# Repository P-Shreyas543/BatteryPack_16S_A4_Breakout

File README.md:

# 14S 18650 Battery Pack Breakout (A4)

KiCad 10 project for a 14S (58.8 V max, 50.4 V nominal) 18650 battery pack on a 297 × 210 mm (A4) 4-layer PCB, built as a BMS breakout and training board.

## Layout architecture
- **Cells:** two mirrored columns of 7. Cells 1–7 run down the left column and cells 8–14 up the right. Every row uses the same **27.6 mm pitch**, so every cell has a 4.8 mm air gap on each side.
- **Equal cell-to-cell resistance (ACIR):** all 13 cell-to-cell links are the same copper strap on F.Cu and B.Cu. The 12 in-column straps are identical 10 mm bars at the holder ends. The cell 7→8 strap across the channel is widened to 16.15 mm so its resistance matches. Checked with a 2-D field solve (`tools/acir.py`, result in `docs/acir_check.txt`): **0.260 mΩ per link, 0.08 % spread**.
- **Centre channel = sense spine.** Each cell node has its own 60 V PPTC right next to it. One routed bus on In1 carries all 15 taps up to J1. NTC pairs run on In2.
- **Top edge = every connection.** Left to right: B− lug · HV indicator + pack TVS · **J1 balance** (centred) · **J2 NTC** · PACK+ lug · fuse.
- **Outer margins = per-cell service area.** Red/black test loops, the reverse-cell LED, and a writable box for cell voltage / IR.

## Symmetry
The board is mirror-symmetric about its vertical centre line. `tools/symcheck.py` lists every footprint without a same-type twin at the mirrored position:
- Mirrored or on the centre line: all 14 holders, the cell straps, the per-cell LED/test-loop groups (the series order of each LED string is chosen so twins use the same parts), the 6 side NTCs, the 12 side PPTCs, the TVS chain under J1, the lugs, holes and fiducials. PPTC 7, NTC4 and J1 sit on the centre line.
- One-of-a-kind, by design: the J2 NTC header (mirrored by the HV indicator + pack TVS block) and the single PACK+ fuse with its blown LED.
- Cell polarity alternates down each column. Because the pack is one series string, the right column's polarity is the reverse of the left's.

## Parts (all JLCPCB / LCSC)
| Block | Parts |
|---|---|
| Cell holders | BH-18650-B1BA002 `C2988620` |
| Per cell | Keystone 5000/5001 test loops (`C5199900` / `C238122`). Reverse-cell LED: 1k `C17513` + red LED `C84256` + 1N4148WS `C2128`. |
| J1 BMS balance | JST XH **B15B-XH-A** `C158020`. Pin 1 = B−, pin 15 = C14+. |
| Tap protection | MF-MSMF010-2 60 V PPTC `C12430` at every node. LKS05D3-B 5 V bidirectional TVS (SOD-323) `C2984829` across every cell, directly under J1. |
| J2 BMS NTC | JST XH **B14B-XH-A** `C158022` with 7× 10k B3950 NTC `C13879` saddled between cells. Pins 2n−1/2n = NTCn. |
| Power path | 5×20 fuse holder `C268205` (fit 10 A), M4 lugs T44009 `C481463`, SMCJ70CA `C840779` |

NTC map: NTC1 = C1/C2, NTC2 = C3/C4, NTC3 = C5/C6 (left column), **NTC4 = board centre line on the cell 7→8 bus**, NTC5 = C13/C14, NTC6 = C11/C12, NTC7 = C9/C10 (right column).

## How to connect
1. Plug the BMS balance lead into **J1** (B− wire on pin 1).
2. Plug the BMS NTC lead into **J2**, or leave it unplugged.
3. Connect the **B− lug** to the BMS B− pad, and the **PACK+ lug** to the load or charger +.
4. Connect the load or charger − to the BMS P−.
5. Insert the cells last. A red LED beside a cell means it is in backwards.

## Files
- `fab/BatteryPack_14S_A4_gerbers.zip`, `fab/JLCPCB_BOM.csv`, `fab/JLCPCB_CPL.csv`: fabrication and assembly files. Check part rotations in JLC's preview.
- `fab/erc.rpt`, `fab/drc.rpt`: 0 ERC violations, 0 DRC violations, 0 unconnected items, 0 schematic-parity issues.
- `docs/`: schematic PDF, renders, and the ACIR check.
- `tools/`: generators. `symcheck.py` runs the symmetry audit. `design.py` holds the parts and nets, `geom.py` the board geometry, `gen_sch.py` / `gen_pcb.py` build the files, and `acir.py` runs the link-resistance check. To rebuild everything, run `tools/build.sh` in the `kicad/kicad:10.0` docker image.

Side-entry XH headers (S15B) are out of stock at LCSC, so the top-entry headers sit right on the top edge. Re-check LCSC stock before ordering. The holder, the test loops and the SOD-323 TVS have the lowest stock.

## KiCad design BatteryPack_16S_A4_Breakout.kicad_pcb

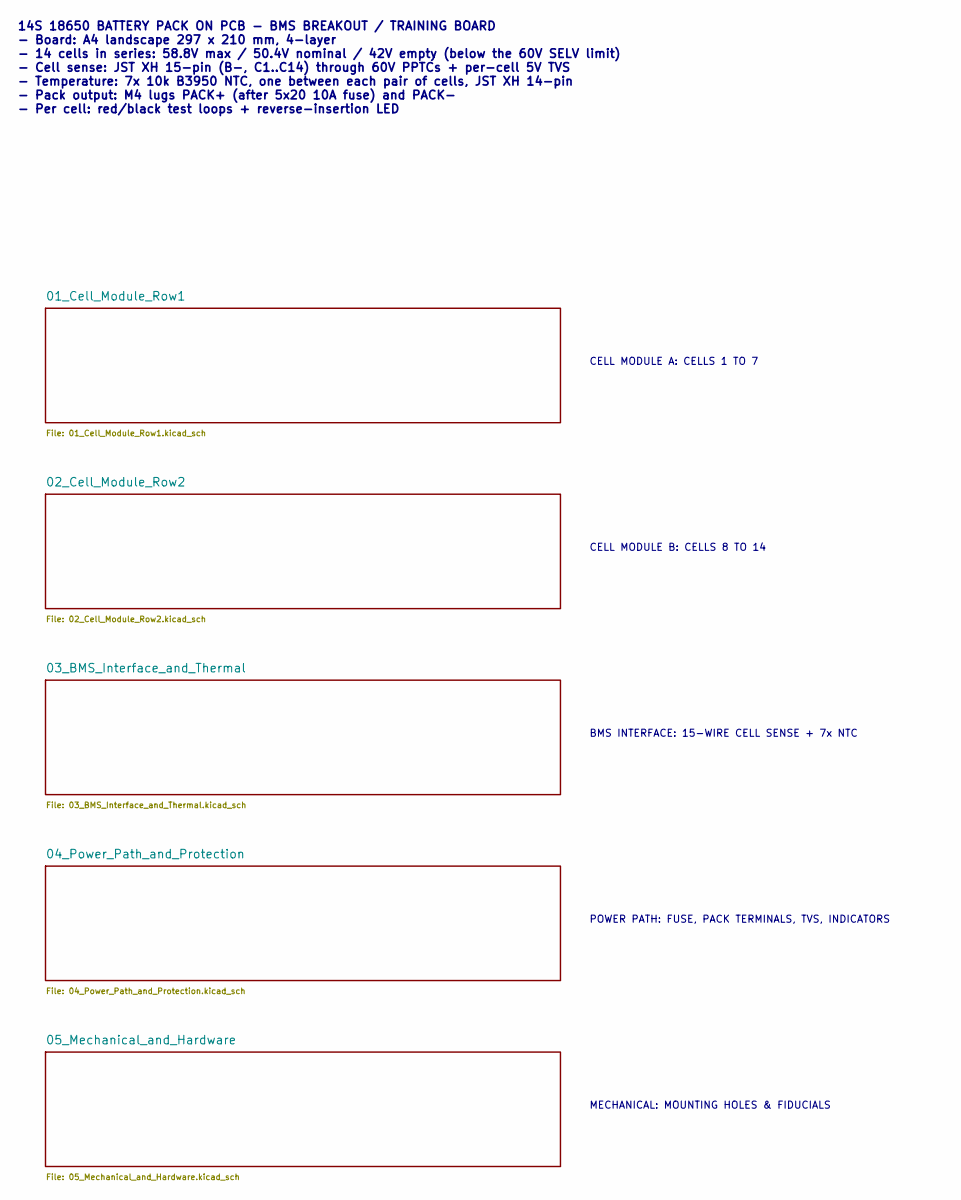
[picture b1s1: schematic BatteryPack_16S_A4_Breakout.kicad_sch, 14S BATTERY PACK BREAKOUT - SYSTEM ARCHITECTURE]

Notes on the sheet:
MECHANICAL: MOUNTING HOLES & FIDUCIALS
CELL MODULE B: CELLS 8 TO 14
BMS INTERFACE: 15-WIRE CELL SENSE + 7x NTC
POWER PATH: FUSE, PACK TERMINALS, TVS, INDICATORS
14S 18650 BATTERY PACK ON PCB - BMS BREAKOUT / TRAINING BOARD - Board: A4 landscape 297 x 210 mm, 4-layer - 14 cells in series: 58.8V max / 50.4V nominal / 42V empty (below the 60V SELV limit) - Cell sense: JST XH 15-pin (B-, C1..C14) through 60V PPTCs + per-cell 5V TVS - Temperature: 7x 10k B3950 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
CELL MODULE A: CELLS 1 TO 7

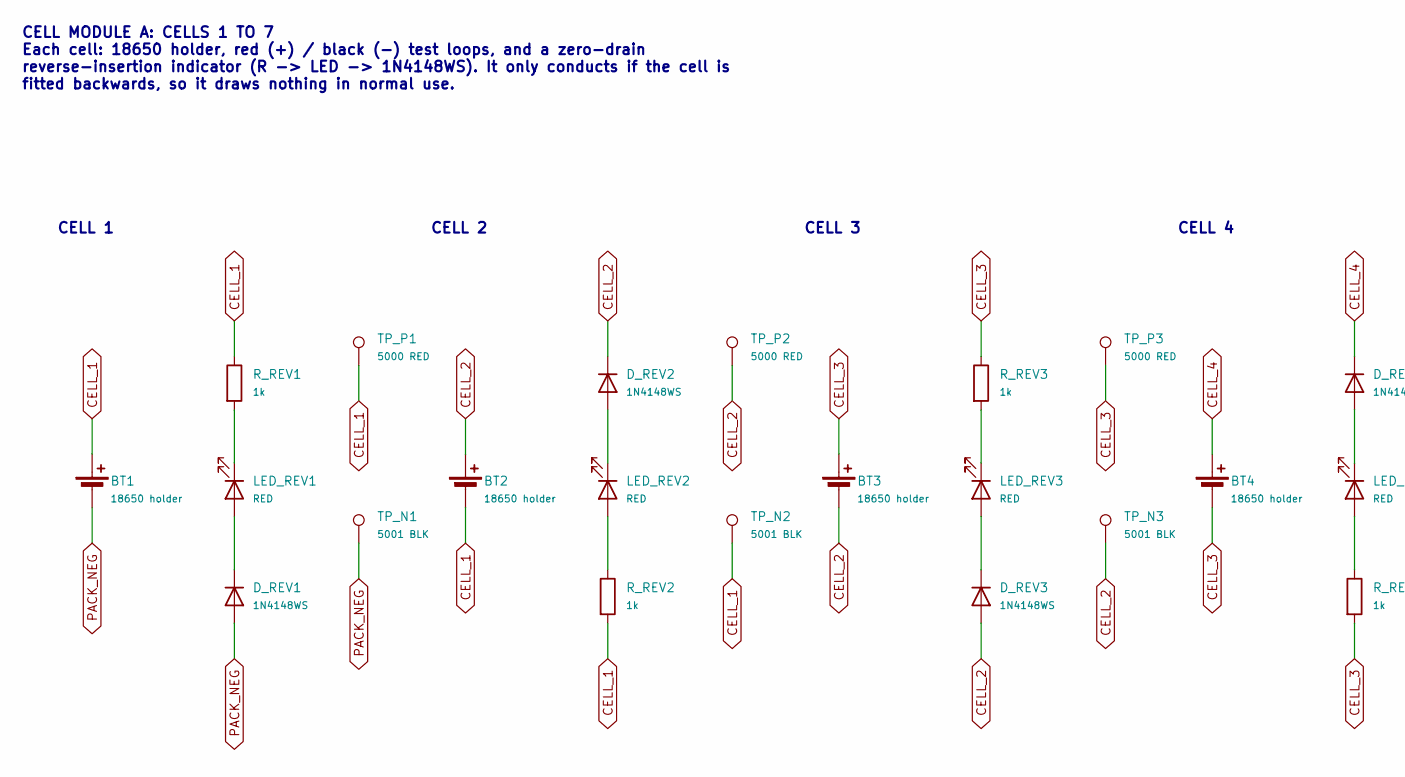
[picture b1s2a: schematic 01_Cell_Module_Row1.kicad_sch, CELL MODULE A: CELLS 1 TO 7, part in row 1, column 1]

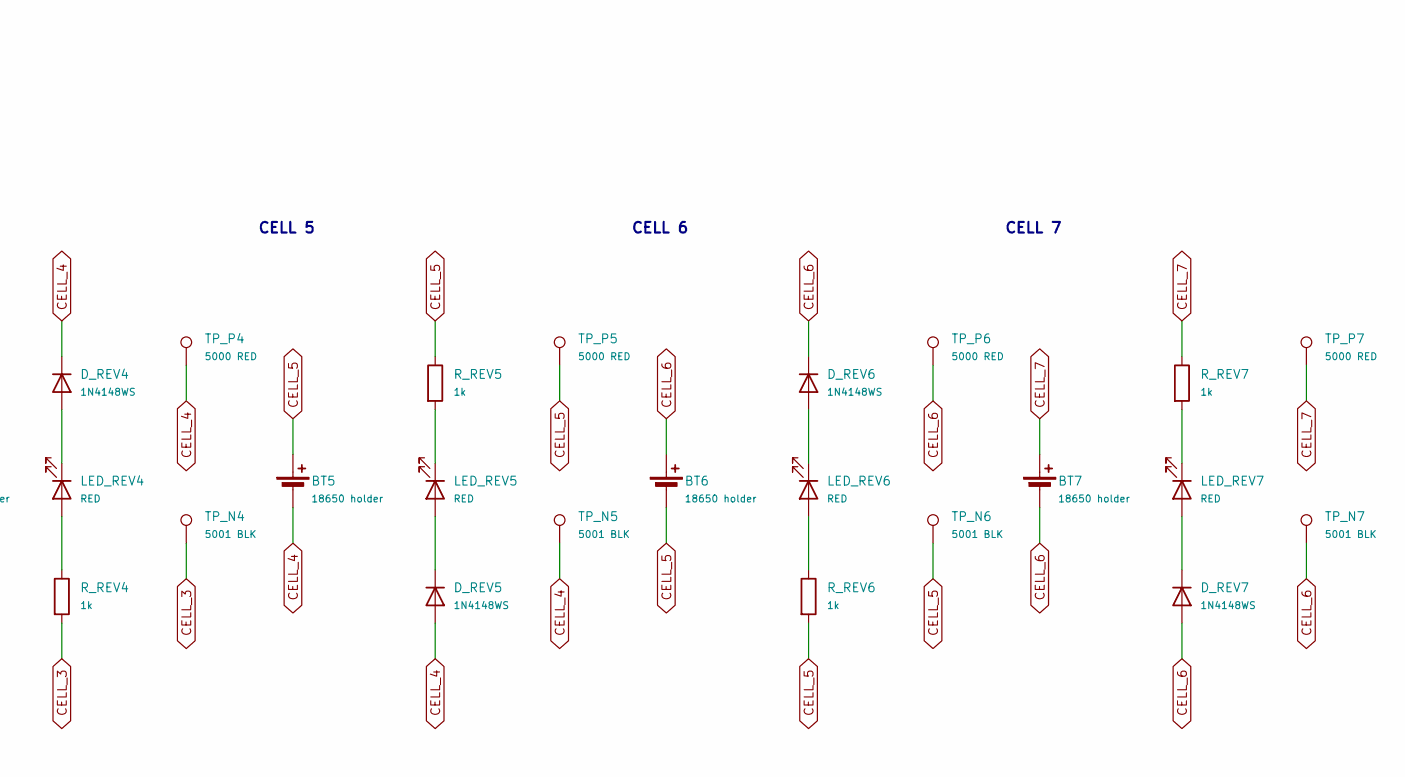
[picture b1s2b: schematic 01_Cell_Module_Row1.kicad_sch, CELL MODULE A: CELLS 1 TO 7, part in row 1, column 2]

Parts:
BT1, BT2, BT3, BT4, BT5, BT6, BT7: 18650 holder; BH18650B1BA002; MPN BH-18650-B1BA002; LCSC C2988620
D_REV1, D_REV2, D_REV3, D_REV4, D_REV5, D_REV6, D_REV7: 1N4148WS; D_SOD-323; MPN 1N4148WS; LCSC C2128
LED_REV1, LED_REV2, LED_REV3, LED_REV4, LED_REV5, LED_REV6, LED_REV7: RED; LED_0805_2012Metric; MPN NCD0805R1; LCSC C84256
R_REV1, R_REV2, R_REV3, R_REV4, R_REV5, R_REV6, R_REV7: 1k; R_0805_2012Metric; MPN 0805W8F1001T5E; LCSC C17513
TP_N1, TP_N2, TP_N3, TP_N4, TP_N5, TP_N6, TP_N7: 5001 BLK; TestPoint_Keystone_5000-5004_Miniature; MPN 5001; LCSC C238122
TP_P1, TP_P2, TP_P3, TP_P4, TP_P5, TP_P6, TP_P7: 5000 RED; TestPoint_Keystone_5000-5004_Miniature; MPN 5000; LCSC C5199900

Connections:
CELL_1: BT1.1 (+), BT2.2 (-), R_REV1.1, R_REV2.2, TP_N2.1, TP_P1.1; also elsewhere on the board
CELL_2: BT2.1 (+), BT3.2 (-), D_REV2.1 (K), D_REV3.2 (A), TP_N3.1, TP_P2.1; also elsewhere on the board
CELL_3: BT3.1 (+), BT4.2 (-), R_REV3.1, R_REV4.2, TP_N4.1, TP_P3.1; also elsewhere on the board
CELL_4: BT4.1 (+), BT5.2 (-), D_REV4.1 (K), D_REV5.2 (A), TP_N5.1, TP_P4.1; also elsewhere on the board
CELL_5: BT5.1 (+), BT6.2 (-), R_REV5.1, R_REV6.2, TP_N6.1, TP_P5.1; also elsewhere on the board
CELL_6: BT6.1 (+), BT7.2 (-), D_REV6.1 (K), D_REV7.2 (A), TP_N7.1, TP_P6.1; also elsewhere on the board
CELL_7: BT7.1 (+), R_REV7.1, TP_P7.1; also elsewhere on the board
unnamed: D_REV1.1 (K), LED_REV1.2 (A)
unnamed: D_REV2.2 (A), LED_REV2.1 (K)
unnamed: D_REV3.1 (K), LED_REV3.2 (A)
unnamed: D_REV4.2 (A), LED_REV4.1 (K)
unnamed: D_REV5.1 (K), LED_REV5.2 (A)
unnamed: D_REV6.2 (A), LED_REV6.1 (K)
unnamed: D_REV7.1 (K), LED_REV7.2 (A)
unnamed: LED_REV1.1 (K), R_REV1.2
unnamed: LED_REV2.2 (A), R_REV2.1
unnamed: LED_REV3.1 (K), R_REV3.2
unnamed: LED_REV4.2 (A), R_REV4.1
unnamed: LED_REV5.1 (K), R_REV5.2
unnamed: LED_REV6.2 (A), R_REV6.1
unnamed: LED_REV7.1 (K), R_REV7.2
PACK_NEG: BT1.2 (-), D_REV1.2 (A), TP_N1.1; also elsewhere on the board

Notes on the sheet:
CELL 4
CELL 2
CELL 7
CELL 3
CELL 5
CELL 6
CELL 1
CELL MODULE A: CELLS 1 TO 7 Each cell: 18650 holder, red (+) / black (-) test loops, and a zero-drain reverse-insertion indicator (R -> LED -> 1N4148WS). It only conducts if the cell is fitted backwards, so it draws nothing in normal use.

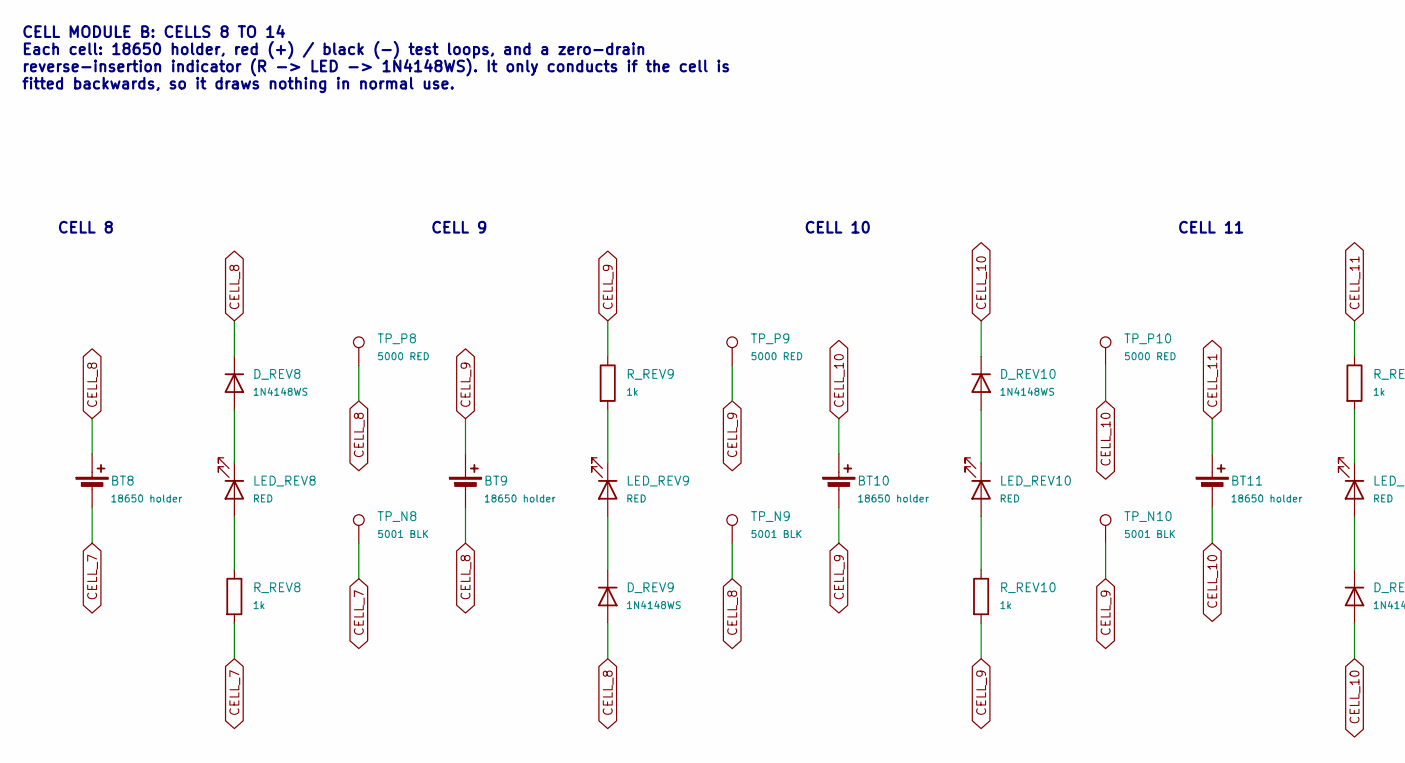
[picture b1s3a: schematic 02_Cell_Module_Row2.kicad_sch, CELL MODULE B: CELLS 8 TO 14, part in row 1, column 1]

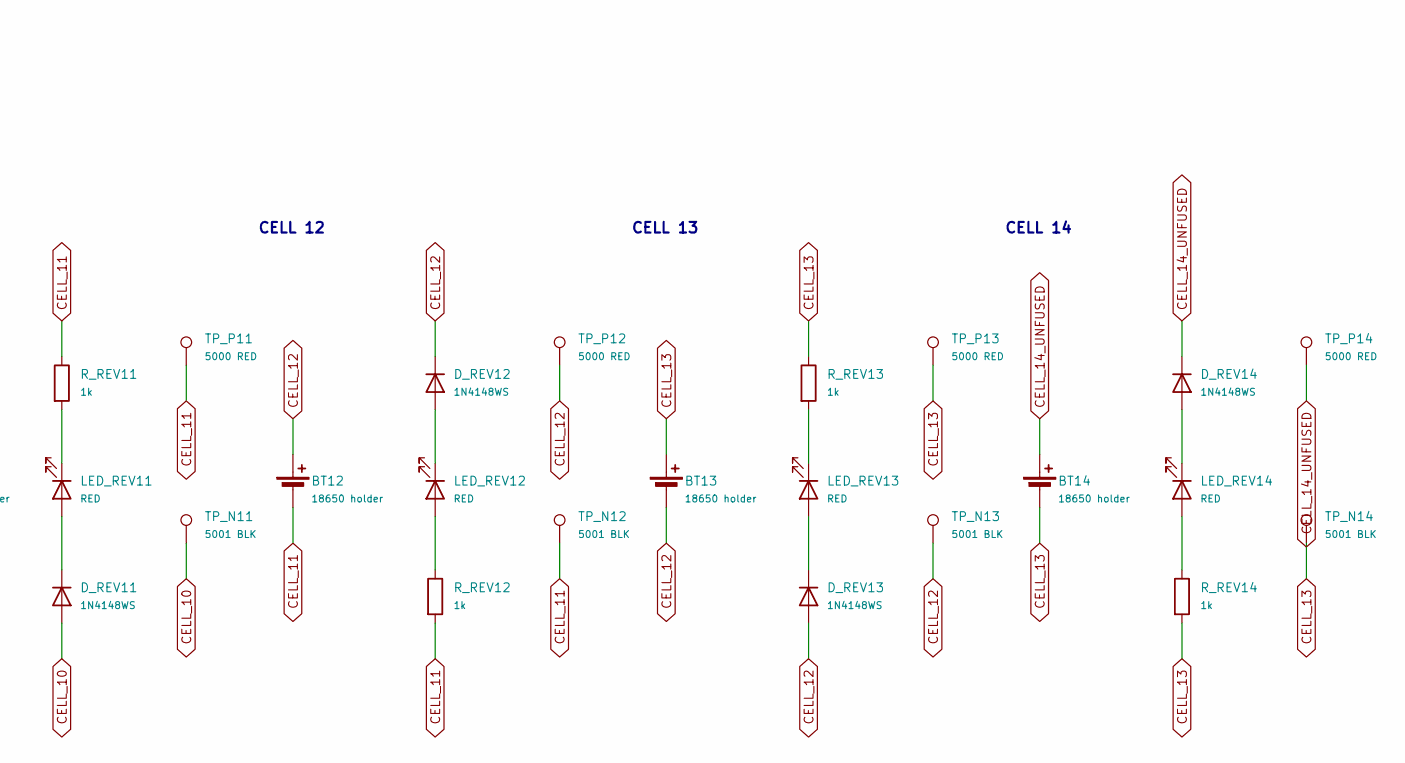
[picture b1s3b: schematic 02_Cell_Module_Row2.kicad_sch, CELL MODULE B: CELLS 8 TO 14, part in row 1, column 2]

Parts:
BT8, BT9, BT10, BT11, BT12, BT13, BT14: 18650 holder; BH18650B1BA002; MPN BH-18650-B1BA002; LCSC C2988620
D_REV8, D_REV9, D_REV10, D_REV11, D_REV12, D_REV13, D_REV14: 1N4148WS; D_SOD-323; MPN 1N4148WS; LCSC C2128
LED_REV8, LED_REV9, LED_REV10, LED_REV11, LED_REV12, LED_REV13, LED_REV14: RED; LED_0805_2012Metric; MPN NCD0805R1; LCSC C84256
R_REV8, R_REV9, R_REV10, R_REV11, R_REV12, R_REV13, R_REV14: 1k; R_0805_2012Metric; MPN 0805W8F1001T5E; LCSC C17513
TP_N8, TP_N9, TP_N10, TP_N11, TP_N12, TP_N13, TP_N14: 5001 BLK; TestPoint_Keystone_5000-5004_Miniature; MPN 5001; LCSC C238122
TP_P8, TP_P9, TP_P10, TP_P11, TP_P12, TP_P13, TP_P14: 5000 RED; TestPoint_Keystone_5000-5004_Miniature; MPN 5000; LCSC C5199900

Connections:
CELL_7: BT8.2 (-), R_REV8.2, TP_N8.1; also elsewhere on the board
CELL_8: BT8.1 (+), BT9.2 (-), D_REV8.1 (K), D_REV9.2 (A), TP_N9.1, TP_P8.1; also elsewhere on the board
CELL_9: BT9.1 (+), BT10.2 (-), R_REV9.1, R_REV10.2, TP_N10.1, TP_P9.1; also elsewhere on the board
CELL_10: BT10.1 (+), BT11.2 (-), D_REV10.1 (K), D_REV11.2 (A), TP_N11.1, TP_P10.1; also elsewhere on the board
CELL_11: BT11.1 (+), BT12.2 (-), R_REV11.1, R_REV12.2, TP_N12.1, TP_P11.1; also elsewhere on the board
CELL_12: BT12.1 (+), BT13.2 (-), D_REV12.1 (K), D_REV13.2 (A), TP_N13.1, TP_P12.1; also elsewhere on the board
CELL_13: BT13.1 (+), BT14.2 (-), R_REV13.1, R_REV14.2, TP_N14.1, TP_P13.1; also elsewhere on the board
CELL_14_UNFUSED: BT14.1 (+), D_REV14.1 (K), TP_P14.1; also elsewhere on the board
unnamed: D_REV8.2 (A), LED_REV8.1 (K)
unnamed: D_REV9.1 (K), LED_REV9.2 (A)
unnamed: D_REV10.2 (A), LED_REV10.1 (K)
unnamed: D_REV11.1 (K), LED_REV11.2 (A)
unnamed: D_REV12.2 (A), LED_REV12.1 (K)
unnamed: D_REV13.1 (K), LED_REV13.2 (A)
unnamed: D_REV14.2 (A), LED_REV14.1 (K)
unnamed: LED_REV8.2 (A), R_REV8.1
unnamed: LED_REV9.1 (K), R_REV9.2
unnamed: LED_REV10.2 (A), R_REV10.1
unnamed: LED_REV11.1 (K), R_REV11.2
unnamed: LED_REV12.2 (A), R_REV12.1
unnamed: LED_REV13.1 (K), R_REV13.2
unnamed: LED_REV14.2 (A), R_REV14.1

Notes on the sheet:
CELL 13
CELL MODULE B: CELLS 8 TO 14 Each cell: 18650 holder, red (+) / black (-) test loops, and a zero-drain reverse-insertion indicator (R -> LED -> 1N4148WS). It only conducts if the cell is fitted backwards, so it draws nothing in normal use.
CELL 9
CELL 14
CELL 12
CELL 8
CELL 10
CELL 11

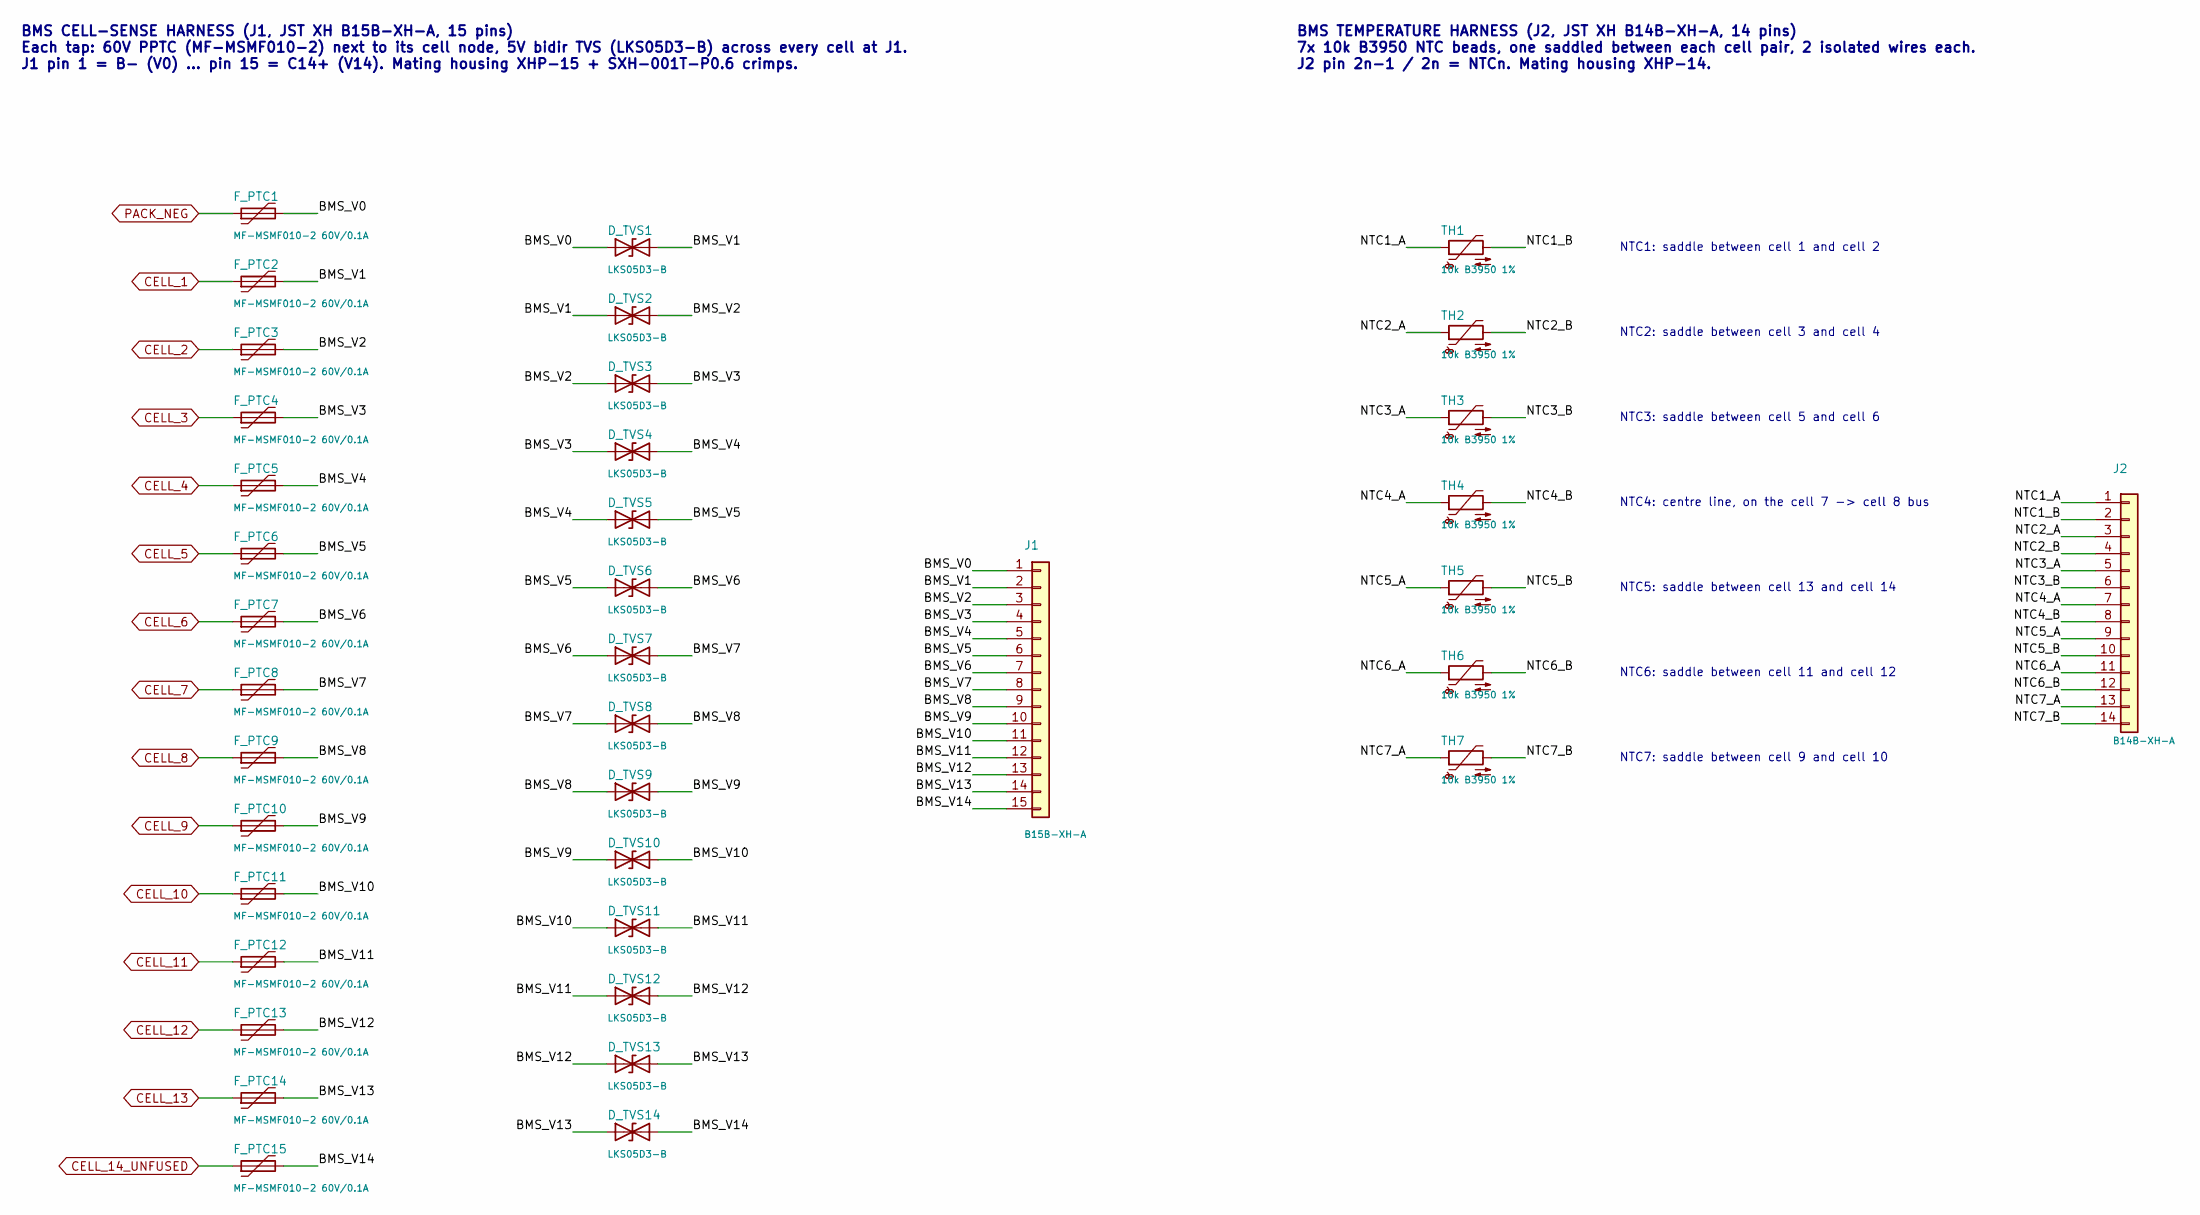
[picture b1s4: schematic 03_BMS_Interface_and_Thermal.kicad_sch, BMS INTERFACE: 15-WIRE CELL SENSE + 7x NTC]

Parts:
D_TVS1, D_TVS2, D_TVS3, D_TVS4, D_TVS5, D_TVS6, D_TVS7, D_TVS8, D_TVS9, D_TVS10, D_TVS11, D_TVS12, D_TVS13, D_TVS14: LKS05D3-B; D_SOD-323; MPN LKS05D3-B; LCSC C2984829
F_PTC1, F_PTC2, F_PTC3, F_PTC4, F_PTC5, F_PTC6, F_PTC7, F_PTC8, F_PTC9, F_PTC10, F_PTC11, F_PTC12, F_PTC13, F_PTC14, F_PTC15: MF-MSMF010-2 60V/0.1A; Fuse_1812_4532Metric; MPN MF-MSMF010-2; LCSC C12430
J1: B15B-XH-A; JST_XH_B15B-XH-A_1x15_P2.50mm_Vertical; MPN B15B-XH-A(LF)(SN); LCSC C158020
J2: B14B-XH-A; JST_XH_B14B-XH-A_1x14_P2.50mm_Vertical; MPN B14B-XH-A(LF)(SN); LCSC C158022
TH1, TH2, TH3, TH4, TH5, TH6, TH7: 10k B3950 1%; R_Axial_DIN0204_L3.6mm_D1.6mm_P2.54mm_Vertical; MPN MF52A103F3950; LCSC C13879

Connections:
/03_BMS_Interface_and_Thermal/BMS_V0: D_TVS1.1 (A1), F_PTC1.2, J1.1
/03_BMS_Interface_and_Thermal/BMS_V1: D_TVS1.2 (A2), D_TVS2.1 (A1), F_PTC2.2, J1.2
/03_BMS_Interface_and_Thermal/BMS_V2: D_TVS2.2 (A2), D_TVS3.1 (A1), F_PTC3.2, J1.3
/03_BMS_Interface_and_Thermal/BMS_V3: D_TVS3.2 (A2), D_TVS4.1 (A1), F_PTC4.2, J1.4
/03_BMS_Interface_and_Thermal/BMS_V4: D_TVS4.2 (A2), D_TVS5.1 (A1), F_PTC5.2, J1.5
/03_BMS_Interface_and_Thermal/BMS_V5: D_TVS5.2 (A2), D_TVS6.1 (A1), F_PTC6.2, J1.6
/03_BMS_Interface_and_Thermal/BMS_V6: D_TVS6.2 (A2), D_TVS7.1 (A1), F_PTC7.2, J1.7
/03_BMS_Interface_and_Thermal/BMS_V7: D_TVS7.2 (A2), D_TVS8.1 (A1), F_PTC8.2, J1.8
/03_BMS_Interface_and_Thermal/BMS_V8: D_TVS8.2 (A2), D_TVS9.1 (A1), F_PTC9.2, J1.9
/03_BMS_Interface_and_Thermal/BMS_V9: D_TVS9.2 (A2), D_TVS10.1 (A1), F_PTC10.2, J1.10
/03_BMS_Interface_and_Thermal/BMS_V10: D_TVS10.2 (A2), D_TVS11.1 (A1), F_PTC11.2, J1.11
/03_BMS_Interface_and_Thermal/BMS_V11: D_TVS11.2 (A2), D_TVS12.1 (A1), F_PTC12.2, J1.12
/03_BMS_Interface_and_Thermal/BMS_V12: D_TVS12.2 (A2), D_TVS13.1 (A1), F_PTC13.2, J1.13
/03_BMS_Interface_and_Thermal/BMS_V13: D_TVS13.2 (A2), D_TVS14.1 (A1), F_PTC14.2, J1.14
/03_BMS_Interface_and_Thermal/BMS_V14: D_TVS14.2 (A2), F_PTC15.2, J1.15
/03_BMS_Interface_and_Thermal/NTC1_A: J2.1, TH1.1
/03_BMS_Interface_and_Thermal/NTC1_B: J2.2, TH1.2
/03_BMS_Interface_and_Thermal/NTC2_A: J2.3, TH2.1
/03_BMS_Interface_and_Thermal/NTC2_B: J2.4, TH2.2
/03_BMS_Interface_and_Thermal/NTC3_A: J2.5, TH3.1
/03_BMS_Interface_and_Thermal/NTC3_B: J2.6, TH3.2
/03_BMS_Interface_and_Thermal/NTC4_A: J2.7, TH4.1
/03_BMS_Interface_and_Thermal/NTC4_B: J2.8, TH4.2
/03_BMS_Interface_and_Thermal/NTC5_A: J2.9, TH5.1
/03_BMS_Interface_and_Thermal/NTC5_B: J2.10, TH5.2
/03_BMS_Interface_and_Thermal/NTC6_A: J2.11, TH6.1
/03_BMS_Interface_and_Thermal/NTC6_B: J2.12, TH6.2
/03_BMS_Interface_and_Thermal/NTC7_A: J2.13, TH7.1
/03_BMS_Interface_and_Thermal/NTC7_B: J2.14, TH7.2
CELL_1: F_PTC2.1; also elsewhere on the board
CELL_2: F_PTC3.1; also elsewhere on the board
CELL_3: F_PTC4.1; also elsewhere on the board
CELL_4: F_PTC5.1; also elsewhere on the board
CELL_5: F_PTC6.1; also elsewhere on the board
CELL_6: F_PTC7.1; also elsewhere on the board
CELL_7: F_PTC8.1; also elsewhere on the board
CELL_8: F_PTC9.1; also elsewhere on the board
CELL_9: F_PTC10.1; also elsewhere on the board
CELL_10: F_PTC11.1; also elsewhere on the board
CELL_11: F_PTC12.1; also elsewhere on the board
CELL_12: F_PTC13.1; also elsewhere on the board
CELL_13: F_PTC14.1; also elsewhere on the board
CELL_14_UNFUSED: F_PTC15.1; also elsewhere on the board
PACK_NEG: F_PTC1.1; also elsewhere on the board

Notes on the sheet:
BMS TEMPERATURE HARNESS (J2, JST XH B14B-XH-A, 14 pins) 7x 10k B3950 NTC beads, one saddled between each cell pair, 2 isolated wires each. J2 pin 2n-1 / 2n = NTCn. Mating housing XHP-14.
NTC6: saddle between cell 11 and cell 12
NTC2: saddle between cell 3 and cell 4
NTC3: saddle between cell 5 and cell 6
NTC5: saddle between cell 13 and cell 14
NTC4: centre line, on the cell 7 -> cell 8 bus
BMS CELL-SENSE HARNESS (J1, JST XH B15B-XH-A, 15 pins) Each tap: 60V PPTC (MF-MSMF010-2) next to its cell node, 5V bidir TVS (LKS05D3-B) across every cell at J1. J1 pin 1 = B- (V0) ... pin 15 = C14+ (V14). Mating housing XHP-15 + SXH-001T-P0.6 crimps.
NTC1: saddle between cell 1 and cell 2
NTC7: saddle between cell 9 and cell 10

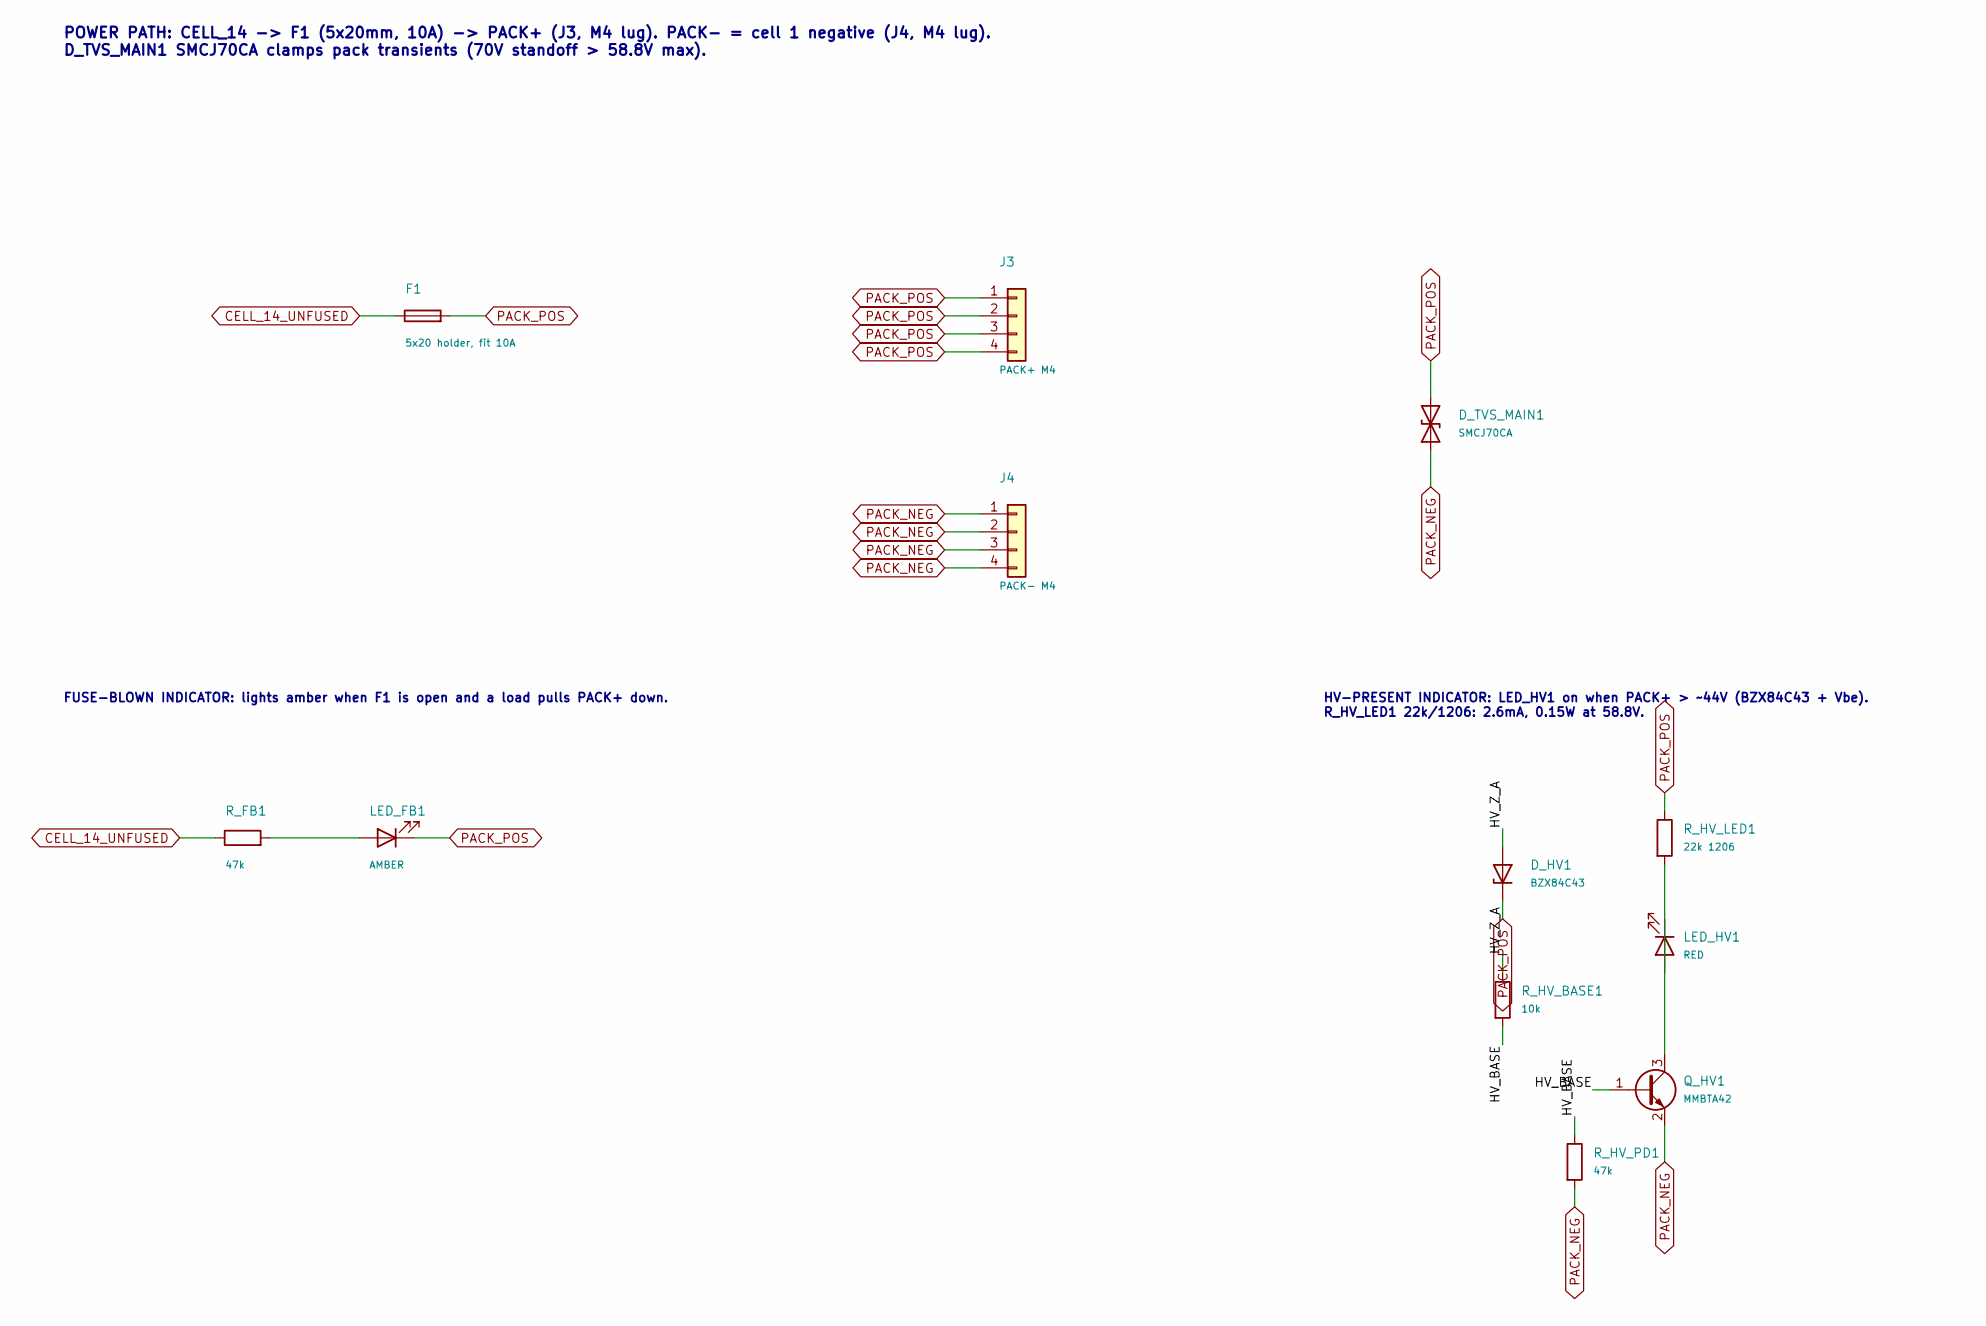
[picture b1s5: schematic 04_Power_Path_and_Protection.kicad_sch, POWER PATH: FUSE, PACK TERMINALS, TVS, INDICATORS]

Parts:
D_HV1: BZX84C43; SOT-23; MPN BZX84C43; LCSC C841170
D_TVS_MAIN1: SMCJ70CA; D_SMC; MPN SMCJ70CA; LCSC C840779
F1: 5x20 holder, fit 10A; FUSE-TH_L24.8-W9.8-P22.60; MPN FH1-200CK-B; LCSC C268205
J3: PACK+ M4; CONN-TH_4P-L11.1-W9.2-P5.00-T44009; MPN T44009; LCSC C481463
J4: PACK- M4; CONN-TH_4P-L11.1-W9.2-P5.00-T44009; MPN T44009; LCSC C481463
LED_FB1: AMBER; LED_0805_2012Metric; MPN KT-0805Y; LCSC C2296
LED_HV1: RED; LED_0805_2012Metric; MPN NCD0805R1; LCSC C84256
Q_HV1: MMBTA42; SOT-23; MPN MMBTA42; LCSC C8515
R_FB1: 47k; R_0805_2012Metric; MPN 0805W8F4702T5E; LCSC C17713
R_HV_BASE1: 10k; R_0805_2012Metric; MPN 0805W8F1002T5E; LCSC C17414
R_HV_LED1: 22k 1206; R_1206_3216Metric; MPN 1206W4F2202T5E; LCSC C25830
R_HV_PD1: 47k; R_0805_2012Metric; MPN 0805W8F4702T5E; LCSC C17713

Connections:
/04_Power_Path_and_Protection/HV_BASE: Q_HV1.1 (B), R_HV_BASE1.2, R_HV_PD1.1
/04_Power_Path_and_Protection/HV_Z_A: D_HV1.1 (A), R_HV_BASE1.1
CELL_14_UNFUSED: F1.1, R_FB1.1; also elsewhere on the board
unnamed: LED_FB1.2 (A), R_FB1.2
PACK_NEG: D_TVS_MAIN1.1 (A1), J4.1, J4.2, J4.3, J4.4, Q_HV1.2 (E), R_HV_PD1.2; also elsewhere on the board
PACK_POS: D_HV1.3 (K), D_TVS_MAIN1.2 (A2), F1.2, J3.1, J3.2, J3.3, J3.4, LED_FB1.1 (K), R_HV_LED1.1

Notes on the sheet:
FUSE-BLOWN INDICATOR: lights amber when F1 is open and a load pulls PACK+ down.
HV-PRESENT INDICATOR: LED_HV1 on when PACK+ > ~44V (BZX84C43 + Vbe). R_HV_LED1 22k/1206: 2.6mA, 0.15W at 58.8V.
POWER PATH: CELL_14 -> F1 (5x20mm, 10A) -> PACK+ (J3, M4 lug). PACK- = cell 1 negative (J4, M4 lug). D_TVS_MAIN1 SMCJ70CA clamps pack transients (70V standoff > 58.8V max).

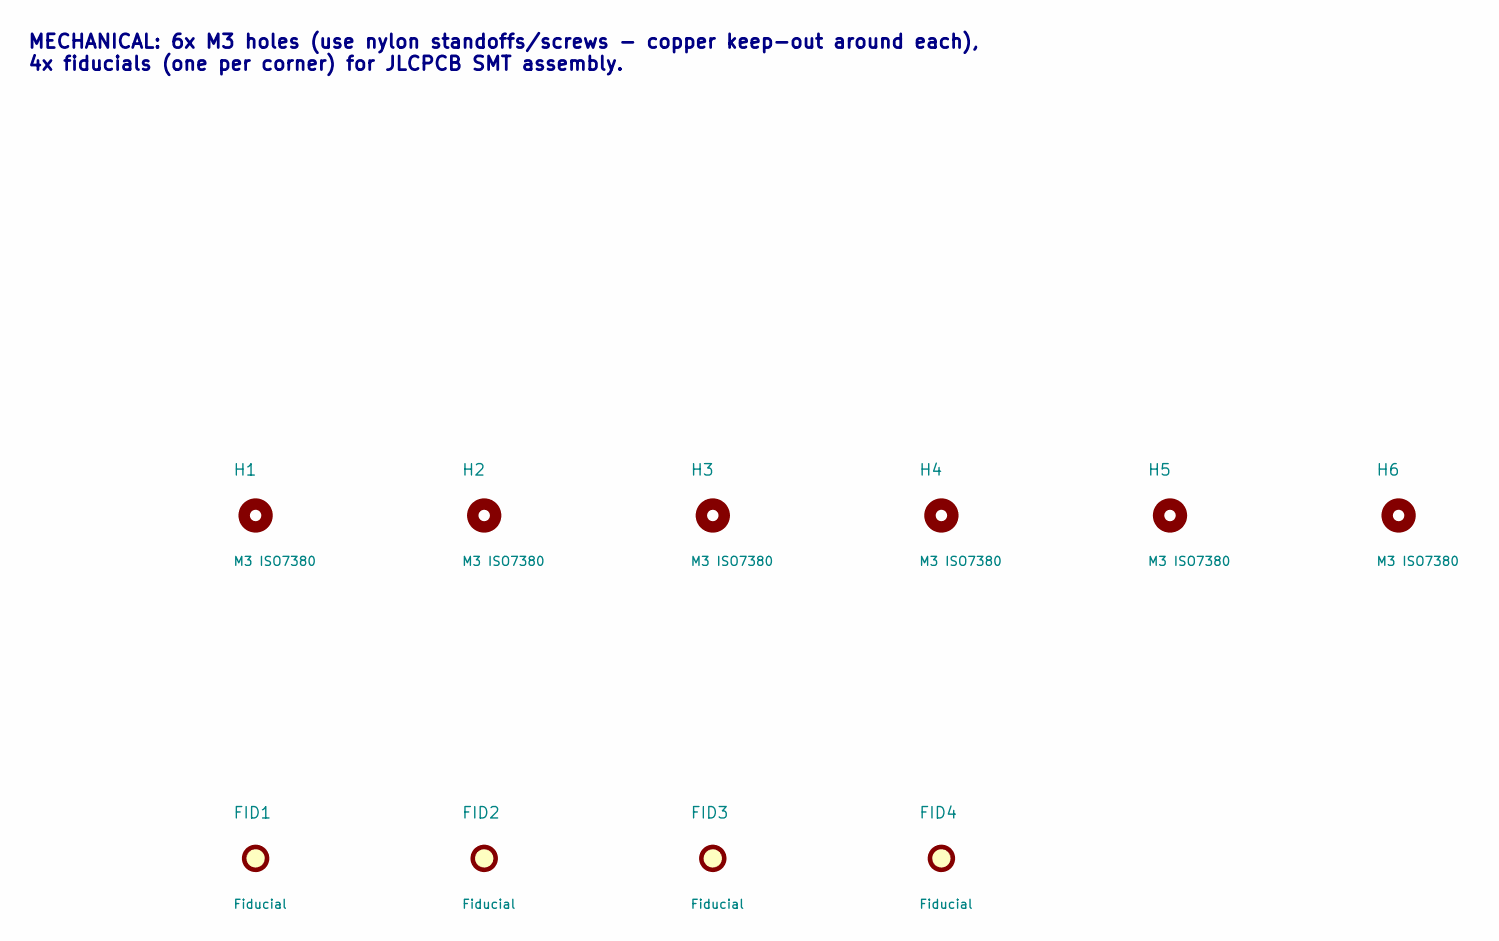
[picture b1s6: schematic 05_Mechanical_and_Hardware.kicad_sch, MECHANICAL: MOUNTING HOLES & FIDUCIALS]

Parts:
FID1, FID2, FID3, FID4: Fiducial; Fiducial_1mm_Mask2mm
H1, H2, H3, H4, H5, H6: M3 ISO7380; MountingHole_3.2mm_M3_ISO7380

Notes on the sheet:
MECHANICAL: 6x M3 holes (use nylon standoffs/screws - copper keep-out around each), 4x fiducials (one per corner) for JLCPCB SMT assembly.

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
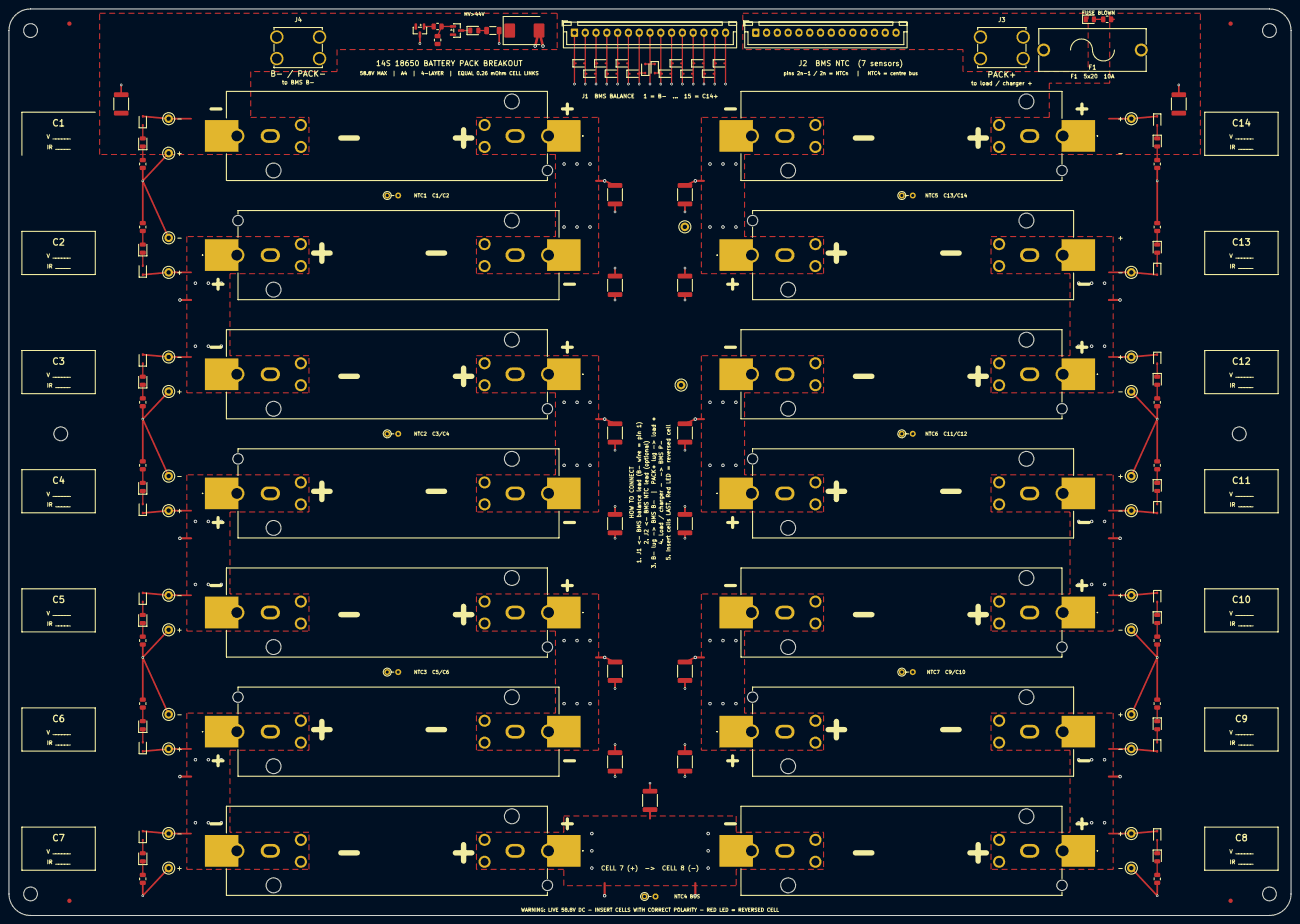
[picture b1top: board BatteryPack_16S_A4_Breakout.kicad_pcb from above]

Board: 4 copper layers, 297.0 x 210.0 mm, 144 parts (0 on the bottom side), 78 nets.

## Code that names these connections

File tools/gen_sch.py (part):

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       "D_TVS_MAIN1 SMCJ70CA clamps pack transients (70V standoff > 58.8V max).", 25.4, 22.86, 1.524, True)
s.place(P["F1"], 76.2, 63.5, 90, ref_off=(-2.54, -3.81), val_off=(-2.54, 3.81))
s.label("F1", "1", design.TOP, 5.08)
s.label("F1", "2", design.PACK_POS, 5.08)
s.place(P["J3"], 160.02, 63.5, 0, ref_off=(-2.54, -7.62), val_off=(-2.54, 7.62))
s.place(P["J4"], 160.02, 93.98, 0, ref_off=(-2.54, -7.62), val_off=(-2.54, 7.62))
for p in "1234":
    s.label("J3", p, design.PACK_POS, 5.08)
    s.label("J4", p, design.PACK_NEG, 5.08)
s.place(P["D_TVS_MAIN1"], 218.44, 78.74, 90, ref_off=(3.81, -1.27), val_off=(3.81, 1.27))
s.label("D_TVS_MAIN1", "1", design.PACK_NEG, 5.08)
s.label("D_TVS_MAIN1", "2", design.PACK_POS, 5.08)

s.text("FUSE-BLOWN INDICATOR: lights amber when F1 is open and a load pulls PACK+ down.", 25.4, 116.84, 1.27, True)
s.place(P["R_FB1"], 50.8, 137.16, 90, ref_off=(-2.54, -3.81), val_off=(-2.54, 3.81))
s.place(P["LED_FB1"], 71.12, 137.16, 180, ref_off=(-2.54, -3.81), val_off=(-2.54, 3.81))
s.label("R_FB1", "1", design.TOP, 5.08)
s.connect(s.pin("R_FB1", "2"), s.pin("LED_FB1", "2"))
s.label("LED_FB1", "1", design.PACK_POS, 5.08)

s.text("HV-PRESENT INDICATOR: LED_HV1 on when PACK+ > ~44V (BZX84C43 + Vbe).\n"
       "R_HV_LED1 22k/1206: 2.6mA, 0.15W at 58.8V.", 203.2, 116.84, 1.27, True)
s.place(P["D_HV1"], 228.6, 142.24, 90, ref_off=(3.81, -1.27), val_off=(3.81, 1.27))
s.label("D_HV1", "3", design.PACK_POS, 2.54)
s.place(P["R_HV_BASE1"], 228.6, 160.02, 0, ref_off=(2.54, -1.27), val_off=(2.54, 1.27))
s.label("D_HV1", "1", "HV_Z_A", 2.54)
s.label("R_HV_BASE1", "1", "HV_Z_A", 2.54)
s.place(P["Q_HV1"], 248.92, 172.72, 0, ref_off=(5.08, -1.27), val_off=(5.08, 1.27))
s.label("R_HV_BASE1", "2", "HV_BASE", 2.54)
s.label("Q_HV1", "1", "HV_BASE", 2.54)
s.place(P["R_HV_PD1"], 238.76, 182.88, 0, ref_off=(2.54, -1.27), val_off=(2.54, 1.27))
s.label("R_HV_PD1", "1", "HV_BASE", 2.54)
s.label("R_HV_PD1", "2", design.PACK_NEG, 2.54)
s.label("Q_HV1", "2", design.PACK_NEG, 5.08)
s.place(P["LED_HV1"], 251.46, 152.4, 270, ref_off=(2.54, -1.27), val_off=(2.54, 1.27))
s.connect(s.pin("LED_HV1", "1"), s.pin("Q_HV1", "3"))
s.place(P["R_HV_LED1"], 251.46, 137.16, 0, ref_off=(2.54, -1.27), val_off=(2.54, 1.27))
s.label("R_HV_LED1", "1", design.PACK_POS, 2.54)
s.connect(s.pin("R_HV_LED1", "2"), s.pin("LED_HV1", "2"))

# ---- mechanical
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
